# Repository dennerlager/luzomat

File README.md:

# luzomat
fully automated luz machine

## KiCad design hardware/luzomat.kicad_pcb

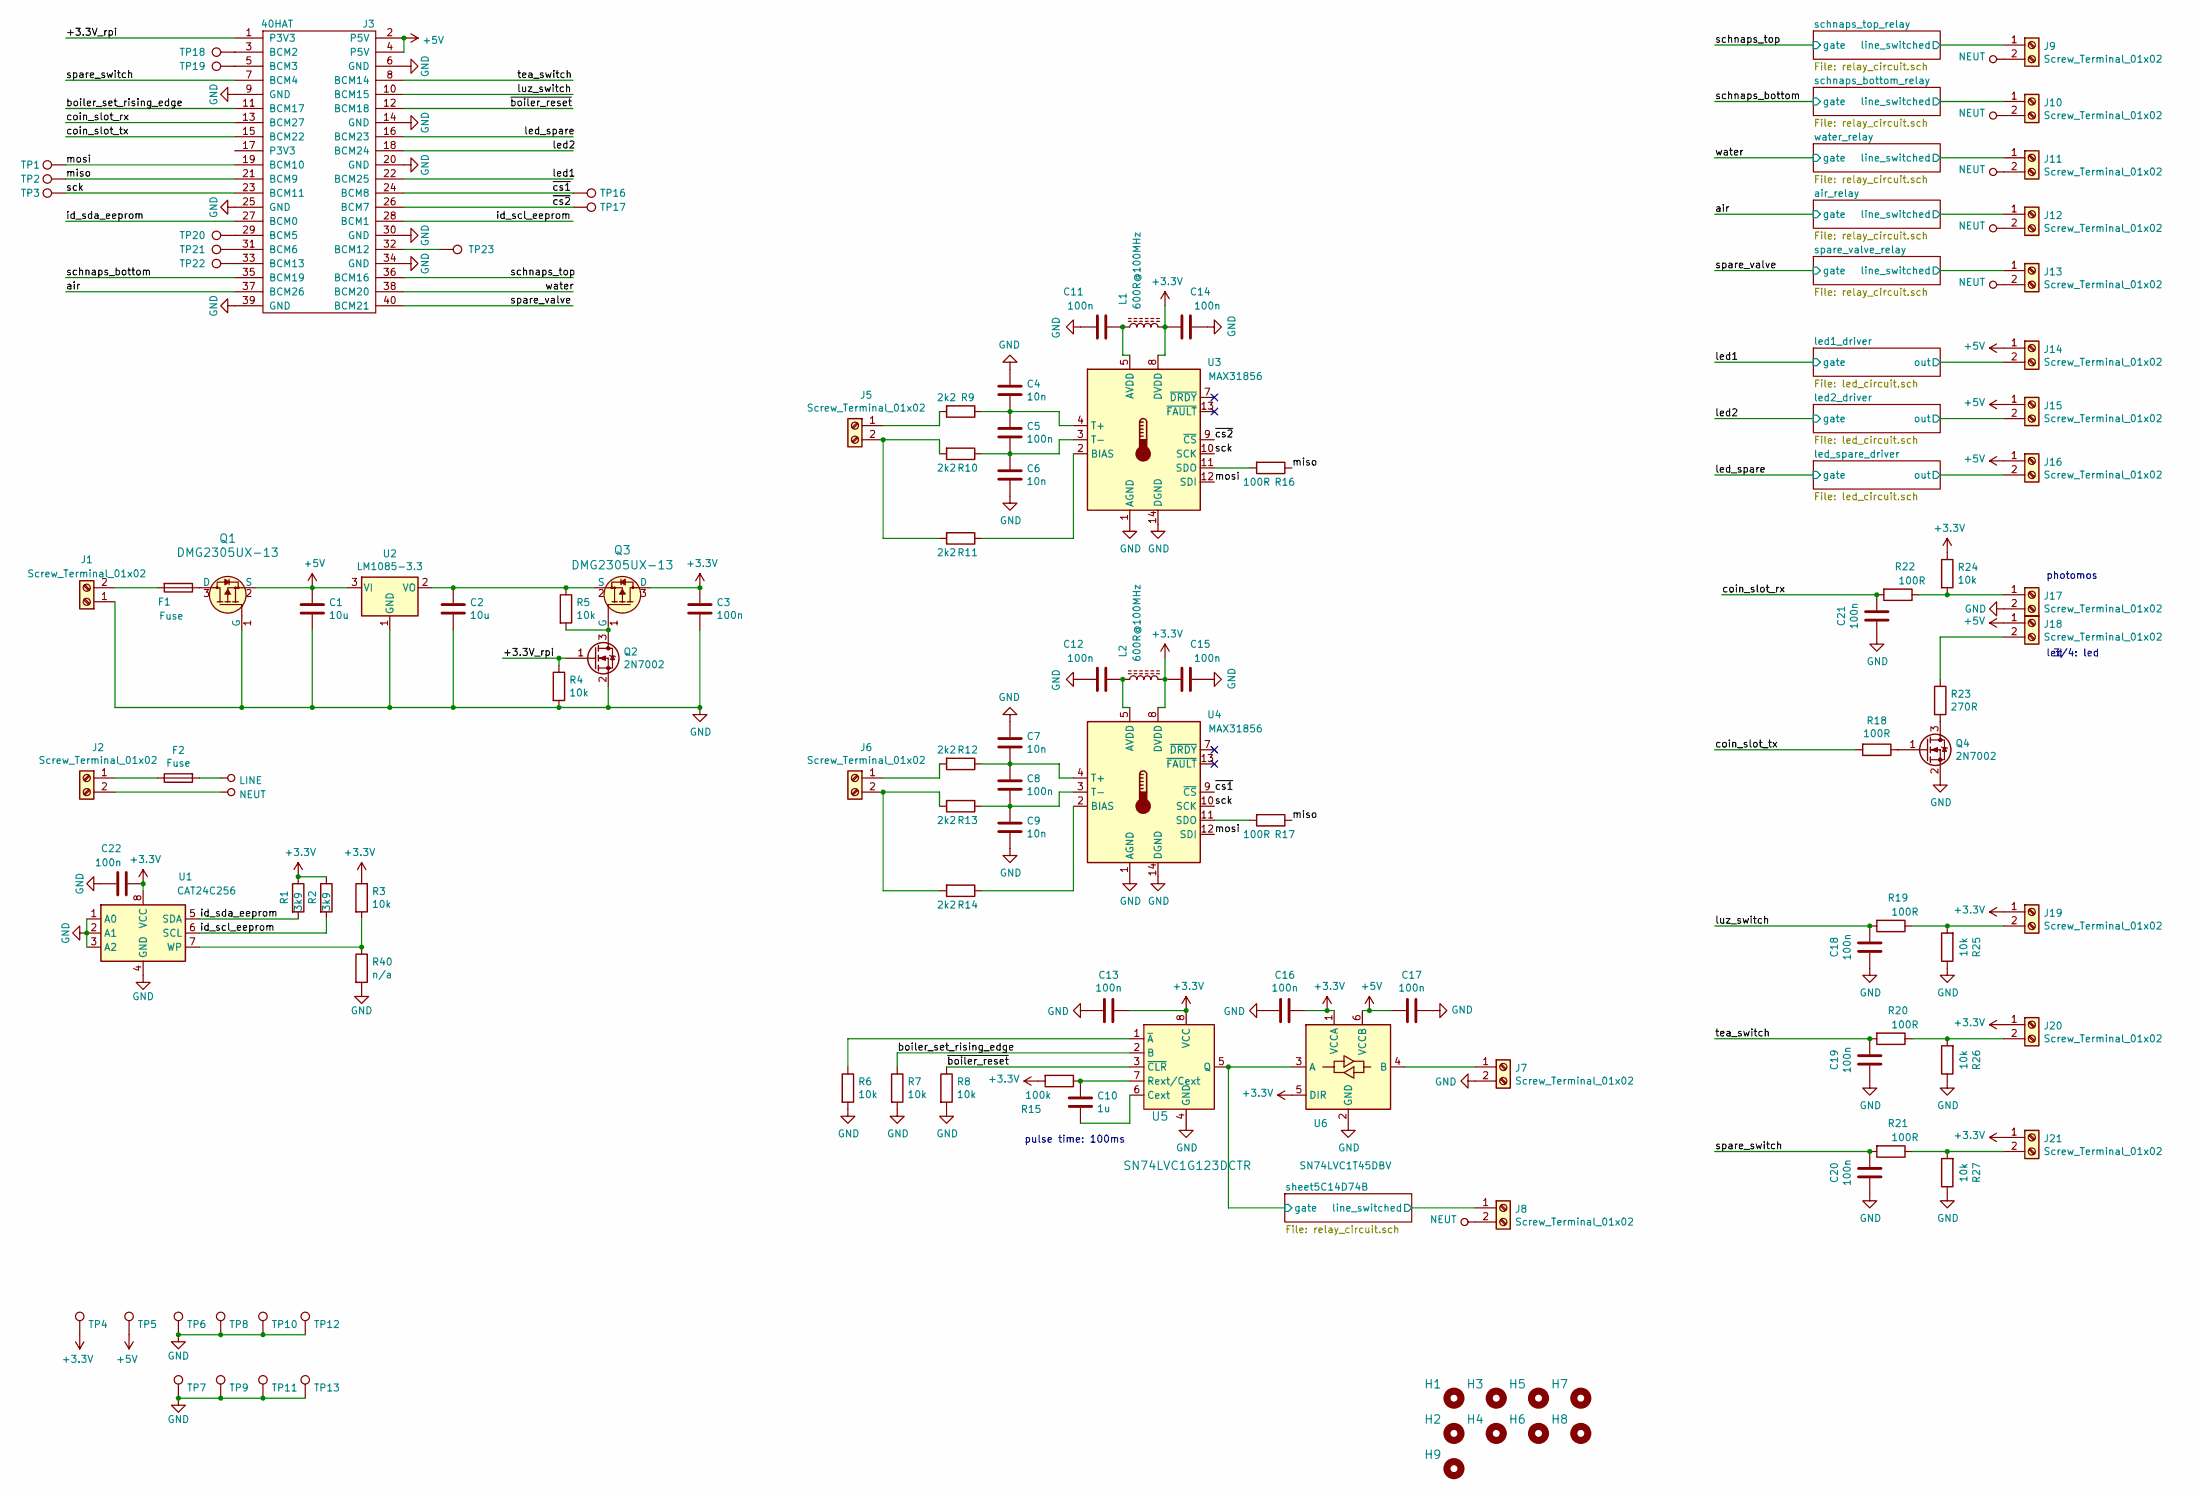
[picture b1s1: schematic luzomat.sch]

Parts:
C1, C2: 10u; C_0805_2012Metric_Pad1.15x1.40mm_HandSolder
C3, C5, C8, C11, C12, C13, C14, C15, C16, C17, C18, C19, C20, C21, C22: 100n; C_0805_2012Metric_Pad1.15x1.40mm_HandSolder
C4, C6, C7, C9: 10n; C_0805_2012Metric_Pad1.15x1.40mm_HandSolder
C10: 1u; C_0805_2012Metric_Pad1.15x1.40mm_HandSolder
F1, F2: Fuse; Fuseholder_Cylinder-5x20mm_Bulgin_FX0457_Horizontal_Closed
H1, H2, H3, H4, H5, H6, H7, H8, H9: 3mm_Mounting_Hole; NPTH_3mm_ID
J1, J2, J5, J6, J7, J8, J9, J10, J11, J12, J13, J14, J15, J16, J17, J18, J19, J20, J21: Screw_Terminal_01x02; TerminalBlock_bornier-2_P5.08mm
J3: 40HAT; PinSocket_2x20_P2.54mm_Vertical
L1, L2: 600R@100MHz; L_0805_2012Metric_Pad1.15x1.40mm_HandSolder
Q1, Q3: DMG2305UX-13; SOT-23-3; MPN DMG2305UX-13; Digi-Key_PN DMG2305UX-13DICT-ND
Q2, Q4: 2N7002; SOT-23
R1, R2: 3k9; R_0805_2012Metric_Pad1.15x1.40mm_HandSolder
R3, R4, R5, R6, R7, R8, R24, R25, R26, R27: 10k; R_0805_2012Metric_Pad1.15x1.40mm_HandSolder
R9, R10, R11, R12, R13, R14: 2k2; R_0805_2012Metric_Pad1.15x1.40mm_HandSolder
R15: 100k; R_0805_2012Metric_Pad1.15x1.40mm_HandSolder
R16, R17, R18, R19, R20, R21, R22: 100R; R_0805_2012Metric_Pad1.15x1.40mm_HandSolder
R23: 270R; R_0805_2012Metric_Pad1.15x1.40mm_HandSolder
R40: n/a; R_0805_2012Metric_Pad1.15x1.40mm_HandSolder
TP1, TP2, TP3, TP4, TP5, TP6, TP7, TP8, TP9, TP10, TP11, TP12, TP13, TP16, TP17, TP18, TP19, TP20, TP21, TP22, TP23: TestPoint; TestPoint_THTPad_D2.5mm_Drill1.2mm
U1: CAT24C256; SOIC-8_3.9x4.9mm_P1.27mm
U2: LM1085-3.3; TO-220-3_Horizontal_TabDown
U3, U4: MAX31856; TSSOP-14_4.4x5mm_P0.65mm
U5: SN74LVC1G123DCTR; MSOP-8_W2.80mm; MPN SN74LVC1G123DCTR; Digi-Key_PN 296-18758-1-ND
U6: SN74LVC1T45DBV; SOT-23-6

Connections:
+3V3: C3.1, C13.1, C14.2, C15.2, C16.1, C22.2, J19.1, J20.1, J21.1, L1.2, L2.2, Q3.3 (D), R1.1, R2.1, R3.1, R15.2, R24.1, TP4.1, U1.8 (VCC), U3.8 (DVDD), U4.8 (DVDD), U5.8 (VCC), U6.1 (VCCA), U6.5 (DIR)
+5V: C1.1, C17.2, J3.2 (P5V), J3.4 (P5V), J14.1, J15.1, J16.1, J18.1, Q1.2 (S), TP5.1, U2.3 (VI), U6.6 (VCCB); also elsewhere on the board
/+3.3V_rpi: J3.1 (P3V3), Q2.1 (G), R4.1
/air: J3.37 (BCM26); also elsewhere on the board
/air_relay/line_switched: J12.1; also elsewhere on the board
/boiler_set_rising_edge: J3.11 (BCM17), R7.1, U5.2 (B)
/coin_slot_rx: C21.1, J3.13 (BCM27), R22.2
/coin_slot_tx: J3.15 (BCM22), R18.2
/id_scl_eeprom: J3.28 (BCM1), R2.2, U1.6 (SCL)
/id_sda_eeprom: J3.27 (BCM0), R1.2, U1.5 (SDA)
/led1: J3.22 (BCM25); also elsewhere on the board
/led1_driver/out: J14.2; also elsewhere on the board
/led2: J3.18 (BCM24); also elsewhere on the board
/led2_driver/out: J15.2; also elsewhere on the board
/led_spare: J3.16 (BCM23); also elsewhere on the board
/led_spare_driver/out: J16.2; also elsewhere on the board
/luz_switch: C18.1, J3.10 (BCM15), R19.2
/miso: J3.21 (BCM9), R16.1, R17.1, TP2.1
/mosi: J3.19 (BCM10), TP1.1, U3.12 (SDI), U4.12 (SDI)
/schnaps_bottom: J3.35 (BCM19); also elsewhere on the board
/schnaps_bottom_relay/line_switched: J10.1; also elsewhere on the board
/schnaps_top: J3.36 (BCM16); also elsewhere on the board
/schnaps_top_relay/line_switched: J9.1; also elsewhere on the board
/sck: J3.23 (BCM11), TP3.1, U3.10 (SCK), U4.10 (SCK)
/sheet5C14D74B/gate: U5.5 (Q), U6.3 (A); also elsewhere on the board
/sheet5C14D74B/line_switched: J8.1; also elsewhere on the board
/spare_switch: C20.1, J3.7 (BCM4), R21.2
/spare_valve: J3.40 (BCM21); also elsewhere on the board
/spare_valve_relay/line_switched: J13.1; also elsewhere on the board
/tea_switch: C19.1, J3.8 (BCM14), R20.2
/water: J3.38 (BCM20); also elsewhere on the board
/water_relay/line_switched: J11.1; also elsewhere on the board
/~boiler_reset~: J3.12 (BCM18), R8.1, U5.3 (~CLR)
/~cs1: J3.24 (BCM8), TP16.1, U4.9 (~CS)
/~cs2: J3.26 (BCM7), TP17.1, U3.9 (~CS)
GND: C1.2, C2.2, C3.2, C4.1, C6.2, C7.1, C9.2, C11.2, C12.2, C13.2, C14.1, C15.1, C16.2, C17.1, C18.2, C19.2, C20.2, C21.2, C22.1, J1.1, J3.6 (GND), J3.9 (GND), J3.14 (GND), J3.20 (GND), J3.25 (GND), J3.30 (GND), J3.34 (GND), J3.39 (GND), J7.2, J17.2, Q1.1 (G), Q2.2 (S), Q4.2 (S), R4.2, R6.2, R7.2, R8.2, R25.1, R26.1, R27.1, R40.2, TP6.1, TP7.1, TP8.1, TP9.1, TP10.1, TP11.1, TP12.1, TP13.1, U1.1 (A0), U1.2 (A1), U1.3 (A2), U1.4 (GND), U2.1 (GND), U3.1 (AGND), U3.14 (DGND), U4.1 (AGND), U4.14 (DGND), U5.4 (GND), U6.2 (GND); also elsewhere on the board
LINE: F2.2; also elsewhere on the board
NEUT: J2.2, J8.2, J9.2, J10.2, J11.2, J12.2, J13.2
unnamed: C2.1, Q3.2 (S), R5.1, U2.2 (VO)
unnamed: C4.2, C5.1, R9.1, U3.4 (T+)
unnamed: C5.2, C6.1, R10.1, U3.3 (T-)
unnamed: C7.2, C8.1, R12.1, U4.4 (T+)
unnamed: C8.2, C9.1, R13.1, U4.3 (T-)
unnamed: C10.1, R15.1, U5.7 (Rext/Cext)
unnamed: C10.2, U5.6 (Cext)
unnamed: C11.1, L1.1, U3.5 (AVDD)
unnamed: C12.1, L2.1, U4.5 (AVDD)
unnamed: F1.1, Q1.3 (D)
unnamed: F1.2, J1.2
unnamed: F2.1, J2.1
unnamed: J3.3 (BCM2), TP18.1
unnamed: J3.5 (BCM3), TP19.1
unnamed: J3.29 (BCM5), TP20.1
unnamed: J3.31 (BCM6), TP21.1
unnamed: J3.32 (BCM12), TP23.1
unnamed: J3.33 (BCM13), TP22.1
unnamed: J5.1, R9.2
unnamed: J5.2, R10.2, R11.2
unnamed: J6.1, R12.2
unnamed: J6.2, R13.2, R14.2
unnamed: J7.1, U6.4 (B)
unnamed: J17.1, R22.1, R24.2
unnamed: J18.2, R23.1
unnamed: J19.2, R19.1, R25.2
unnamed: J20.2, R20.1, R26.2
unnamed: J21.2, R21.1, R27.2
unnamed: Q2.3 (D), Q3.1 (G), R5.2
unnamed: Q4.1 (G), R18.1
unnamed: Q4.3 (D), R23.2
unnamed: R3.2, R40.1, U1.7 (WP)
unnamed: R6.1, U5.1 (~A)
unnamed: R11.1, U3.2 (BIAS)
unnamed: R14.1, U4.2 (BIAS)
unnamed: R16.2, U3.11 (SDO)
unnamed: R17.2, U4.11 (SDO)

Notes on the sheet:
pulse time: 100ms
photomos
3/4: led
led

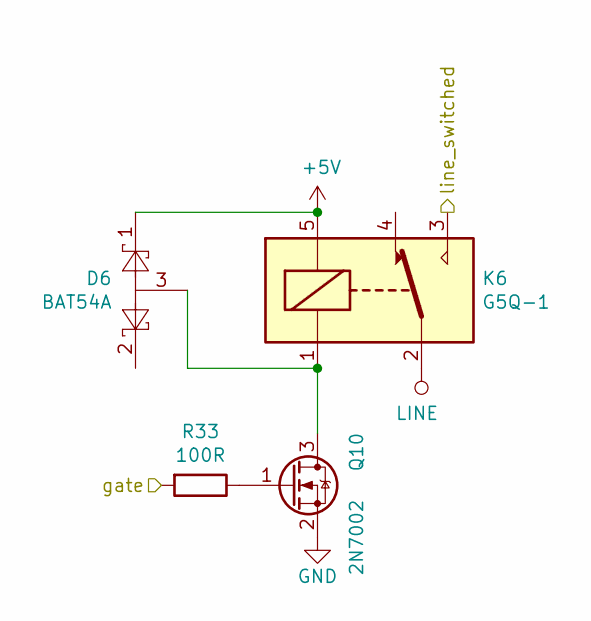
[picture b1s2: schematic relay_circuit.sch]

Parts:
D6: BAT54A; SOT-23
K6: G5Q-1; Relay_SPDT_Omron-G5Q-1
Q10: 2N7002; SOT-23
R33: 100R; R_0805_2012Metric_Pad1.15x1.40mm_HandSolder

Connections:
+5V: D6.1, K6.5; also elsewhere on the board
/schnaps_top: R33.2; also elsewhere on the board
/schnaps_top_relay/line_switched: K6.3; also elsewhere on the board
GND: Q10.2 (S); also elsewhere on the board
LINE: K6.2; also elsewhere on the board
unnamed: D6.3, K6.1, Q10.3 (D)
unnamed: Q10.1 (G), R33.1

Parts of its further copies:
D1, D2, D3, D4, D5: BAT54A; SOT-23
K1, K2, K3, K4, K5: G5Q-1; Relay_SPDT_Omron-G5Q-1
Q5, Q6, Q7, Q8, Q9: 2N7002; SOT-23
R28, R29, R30, R31, R32: 100R; R_0805_2012Metric_Pad1.15x1.40mm_HandSolder

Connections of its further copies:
+5V: D1.1, D2.1, D3.1, D4.1, D5.1, K1.5, K2.5, K3.5, K4.5, K5.5; also elsewhere on the board
/air: R30.2; also elsewhere on the board
/air_relay/line_switched: K3.3; also elsewhere on the board
/schnaps_bottom: R32.2; also elsewhere on the board
/schnaps_bottom_relay/line_switched: K5.3; also elsewhere on the board
/sheet5C14D74B/gate: R28.2; also elsewhere on the board
/sheet5C14D74B/line_switched: K1.3; also elsewhere on the board
/spare_valve: R29.2; also elsewhere on the board
/spare_valve_relay/line_switched: K2.3; also elsewhere on the board
/water: R31.2; also elsewhere on the board
/water_relay/line_switched: K4.3; also elsewhere on the board
GND: Q5.2 (S), Q6.2 (S), Q7.2 (S), Q8.2 (S), Q9.2 (S); also elsewhere on the board
LINE: K1.2, K2.2, K3.2, K4.2, K5.2; also elsewhere on the board
unnamed: D1.3, K1.1, Q5.3 (D)
unnamed: D2.3, K2.1, Q6.3 (D)
unnamed: D3.3, K3.1, Q7.3 (D)
unnamed: D4.3, K4.1, Q8.3 (D)
unnamed: D5.3, K5.1, Q9.3 (D)
unnamed: Q5.1 (G), R28.1
unnamed: Q6.1 (G), R29.1
unnamed: Q7.1 (G), R30.1
unnamed: Q8.1 (G), R31.1
unnamed: Q9.1 (G), R32.1

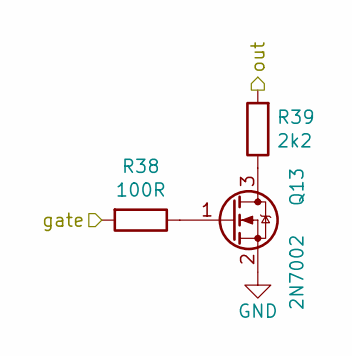
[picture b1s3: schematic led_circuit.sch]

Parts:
Q11: 2N7002; SOT-23
R34: 100R; R_0805_2012Metric_Pad1.15x1.40mm_HandSolder
R35: 2k2; R_0805_2012Metric_Pad1.15x1.40mm_HandSolder

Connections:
/led1: R34.2; also elsewhere on the board
/led1_driver/out: R35.2; also elsewhere on the board
GND: Q11.2 (S); also elsewhere on the board
unnamed: Q11.1 (G), R34.1
unnamed: Q11.3 (D), R35.1

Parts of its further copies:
Q12, Q13: 2N7002; SOT-23
R36, R38: 100R; R_0805_2012Metric_Pad1.15x1.40mm_HandSolder
R37, R39: 2k2; R_0805_2012Metric_Pad1.15x1.40mm_HandSolder

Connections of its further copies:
/led2: R36.2; also elsewhere on the board
/led2_driver/out: R37.2; also elsewhere on the board
/led_spare: R38.2; also elsewhere on the board
/led_spare_driver/out: R39.2; also elsewhere on the board
GND: Q12.2 (S), Q13.2 (S); also elsewhere on the board
unnamed: Q12.1 (G), R36.1
unnamed: Q12.3 (D), R37.1
unnamed: Q13.1 (G), R38.1
unnamed: Q13.3 (D), R39.1

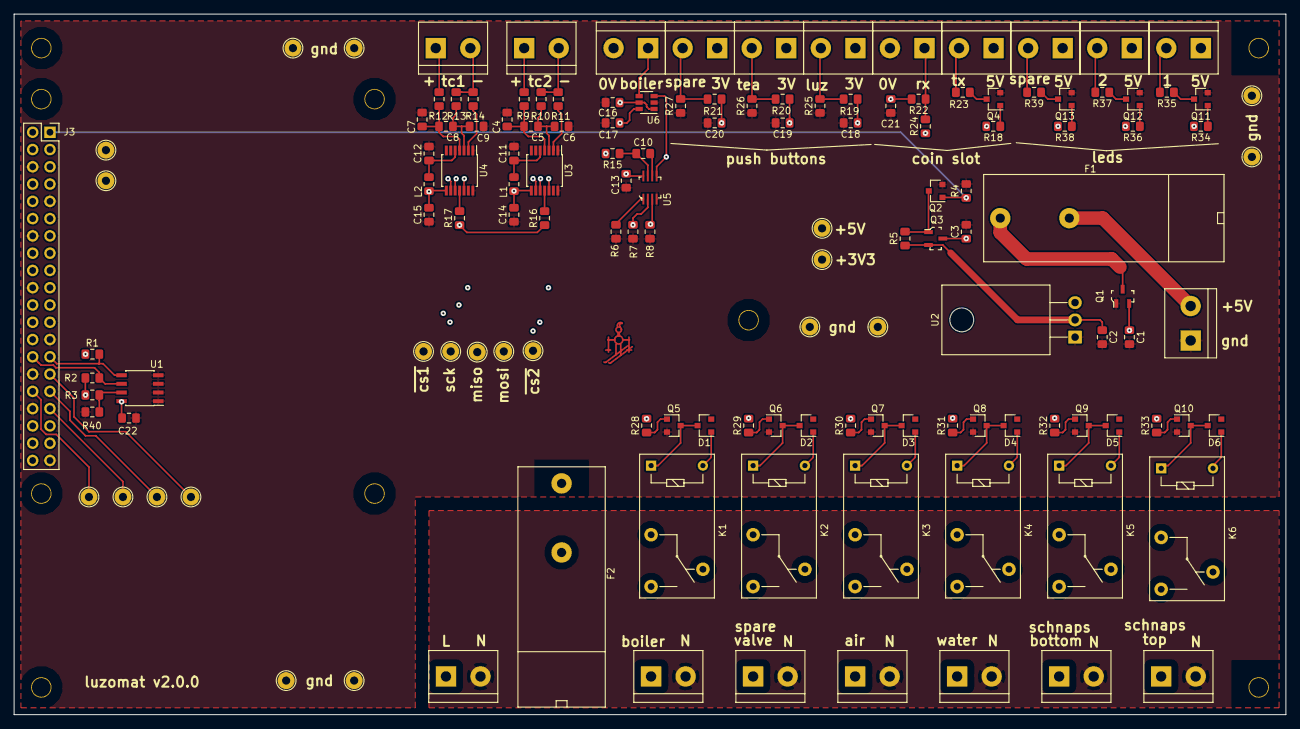
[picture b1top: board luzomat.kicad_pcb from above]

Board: 4 copper layers, 187.0 x 103.0 mm, 147 parts (0 on the bottom side), 93 nets.

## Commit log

2018-12-09 first check in of schematic files
    still work in progress
2019-01-13 layout first draft
2019-01-13 added testpoints and silkscreen
2019-01-16 added skier, ordered pcb
